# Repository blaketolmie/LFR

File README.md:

# LFR
ENMT221 Line Following Robot Software  
S2 2024  

## Access to Github
Send me your GitHub username or email so I can grant you collaborater access (so you can make push and pull requests etc)  
[GitHub Desktop](https://github.com/apps/desktop)

## Set up  
Download [MiniCore](https://github.com/MCUdude/MiniCore#how-to-install) and make sure its in the correct folder   
Open [Arduino IDE](https://www.arduino.cc/en/software)  
Select Board - ATmega328 and port  
Go to tools and select preferences and burn bootloader  
+ Board: "ATmega328"  
+ BOD (Brown-out detection): "BOD 2.7V"  
+ Bootloader: "Yes (UART0)"  
+ Clock: "Internal 1 MHz"  
+ Variant: "328P / 328PA"  
+ Programmer: "Atmel-ICE ISP"  
>**Arduino as ISP**: If you have an Arduino board, you can use it to program AVR chips by setting it up as an ISP (In-System Programmer). This is a common and cost-effective method.  
>USBasp: This is a popular and inexpensive USB-based programmer for AVR microcontrollers. It's widely used and works well with AVR GCC.  
>USBtinyISP: Another inexpensive USB programmer. It’s often used with AVR microcontrollers but might be slower than USBasp.  
>AVRISP mkII: This is an official programmer from Atmel (now Microchip) designed for use with AVR microcontrollers. It is a reliable choice if you have access to it.  
>Clock: 9.216 MHz  
>[Arduino Programming](https://docs.arduino.cc/programming/)  
>When coding in Arduino IDE use [Arduino Pins](https://camo.githubusercontent.com/b719fa994f4db0dd95e224fbdd939f93f7b6ba881b3c41e480b4733d4d82b6e6/68747470733a2f2f692e696d6775722e636f6d2f715849456368542e6a7067) in blue  
  
## Arduino_Code
Incorporated  
- Reactive control  
- LEDs  
- Sensors  
- Motors  
- Config file - all #defines for pin and globals  
- Serial communication (println)  
  
NOTE:  
Only one reset button (MOTOR_CONTROL) is available since the RESET button is not connect to the microcontroller in the schematic.  
If sensors are giving random values - check the height from the ground  
Only 3 sensors ended up working hence no PID or bang bang controller  
  
 ## ATMega328P Microcontroller
[ATMega328P Features Datasheet](https://components101.com/microcontrollers/atmega328p-pinout-features-datasheet)  
[ATMega328P Manufacteres Datasheet - register summary on pg8](https://www.jameco.com/Jameco/Products/ProdDS/2139111.pdf)

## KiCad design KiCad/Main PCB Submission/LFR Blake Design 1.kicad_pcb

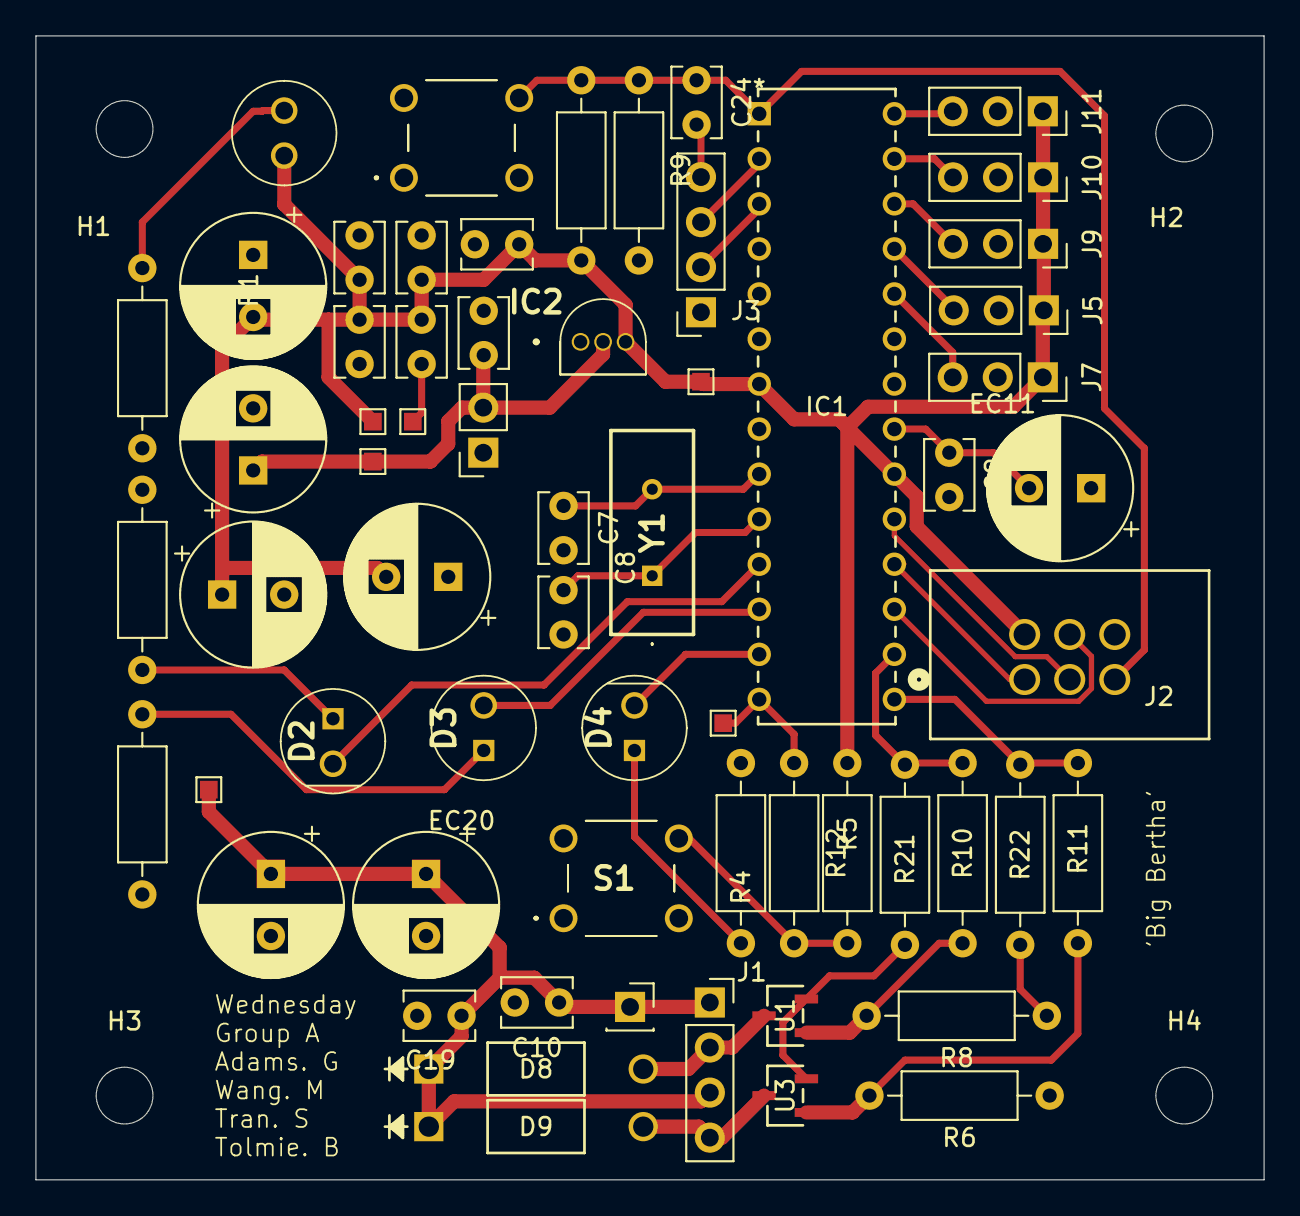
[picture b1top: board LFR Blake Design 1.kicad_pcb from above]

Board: 2 copper layers, 69.2 x 64.5 mm, 66 parts (0 on the bottom side), 34 nets.

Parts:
C2, C3, C5, C9, C14: 100nF; C_Disc_D3.8mm_W2.6mm_P2.50mm
C7, C8: 20pF; C_Disc_D3.8mm_W2.6mm_P2.50mm
C10, C19: 100n; C_Disc_D3.8mm_W2.6mm_P2.50mm
C24: 0.1u; C_Disc_D3.8mm_W2.6mm_P2.50mm
Cm1, Cm2: 100nF; C_Disc_D3.8mm_W2.6mm_P2.50mm
D1: LED; 151051VS04000
D2, D3, D4: LED; 151051BS04000
D8, D9: 1N4004; Diode
EC1, EC4: 10uF; CP_Radial_D8.0mm_P3.50mm
EC11, EC16, EC17: 1uF; CP_Radial_D8.0mm_P3.50mm
EC20, EC21: 100u; CP_Radial_D8.0mm_P3.50mm
H1, H2, H3, H4: MountingHole; MountingHole_3.2mm_M3
IC1: ATMEGA328-PU; Microcontroller
IC2: MCP1700-3302E_TO; MCP17003302ETO
J1: Motor Inputs; PinSocket_1x04_P2.54mm_Vertical
J2: AVR-ISP-6; CONN_WR-BHD_61200621621_WRE
J3: Conn_01x04; PinSocket_1x04_P2.54mm_Vertical
J5, J7, J9, J10, J11: Conn_01x03; PinSocket_1x03_P2.54mm_Vertical
J6: Conn_01x02_Pin; PinSocket_1x02_P2.54mm_Vertical
J8: UnREG; PinSocket_1x01_P2.54mm_Vertical
R1: 360R; Throughhole Resistor
R2, R3, R4: 130; Throughhole Resistor
R5, R7, R21, R22: 10k; Throughhole Resistor
R6, R8, R10, R11: R; Throughhole Resistor
R9, R12: 1k; Throughhole Resistor
S1, S2: MJTP1230
TP1, TP1#2, TP3, TP4, TP5, TP6: TestPoint; TestPoint_Pad_1.0x1.0mm
U1, U3: BSR802NL6327HTSA1; Surface Mount MOSFET
Y1: HC-49_U-S9216000ABJB; HC49US9216000ABJB

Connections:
AVCC: C3.1, C5.1, C14.1, Cm1.1, Cm2.1, D1.2 (A), EC4.1, EC16.2, EC17.2, IC1.7 (VCC), IC1.20 (AVCC), IC2.3 (VOUT), J2.2 (VCC), J5.1, J7.1, J9.1, J10.1, J11.1, R5.2, R7.2, TP1.5 (1), TP3.1
GND: C2.2, C3.2, C5.2, C7.2, C8.2, C9.2, C10.2, C14.2, C19.2, Cm1.2, Cm2.2, EC1.2, EC4.2, EC11.1, EC16.1, EC17.1, EC20.2, EC21.2, IC1.8 (GND_1), IC1.22 (GND_2), IC2.1 (GND), J2.6 (GND), J3.1, J5.2, J6.1, J7.2, J9.2, J10.2, J11.2, R1.2, R2.2, R3.2, R4.2, R6.1, R8.1, R21.1, R22.1, S1.1 (COM_1), S1.4 (NO_2), S2.1 (COM_1), S2.4 (NO_2), TP1#2.1, U1.2, U3.2
MISO: IC1.18 (PB4_(MISO/PCINT4)), J2.1 (MISO)
MOSI: IC1.17 (PB3_(MOSI/OC2A/PCINT3)), J2.4 (MOSI)
MOTOR_CONTROL: IC1.14 ((PCINT0/CLKO/ICP1)_PB0), R12.1, TP4.1
Motor 1: IC1.15 (PB1_(OC1A/PCINT1)), R11.1, R22.2
Motor 2: IC1.16 (PB2_(SS/OC1B/PCINT2)), R10.2, R21.2
unnamed: D1.1 (K), R1.1
unnamed: D2.1 (K), R2.1
unnamed: D3.1 (K), R3.1
unnamed: D4.1 (K), R4.1
unnamed: D8.2 (A), J1.2, U1.3
unnamed: C10.1, C19.1, D8.1 (K), D9.1 (K), EC20.1, EC21.1, J1.1, J1.3, J8.1, TP5.1
unnamed: D9.2 (A), J1.4, U3.3
unnamed: IC1.2 ((PCINT16/RXD)_PD0), J3.3
unnamed: IC1.3 ((PCINT17/TXD)_PD1), J3.2
unnamed: C9.1, EC11.2, IC1.21 (AREF)
unnamed: C24.2, J3.4
unnamed: R8.2, R10.1, U1.1
unnamed: R6.2, R11.2, U3.1
unnamed: R5.1, R12.2, S1.3 (NO_1)
RESET: C24.1, IC1.1 ((PCINT14/RESET)_PC6), J2.5 (~RST), R7.1, R9.1, S2.3 (NO_1)
SCK: IC1.19 (PB5_(SCK/PCINT5)), J2.3 (SCK)
STAT1: D2.2 (A), IC1.11 ((PCINT21/OC0B/T1)_PD5)
STAT2: D3.2 (A), IC1.12 ((PCINT22/OC0A/AIN0)_PD6)
STAT3: D4.2 (A), IC1.13 ((PCINT23/AIN1)_PD7)
Sensor1: IC1.28 (PC5_(ADC5/SCL/PCINT13)), J11.3
Sensor2: IC1.27 (PC4_(ADC4/SDA/PCINT12)), J10.3
Sensor3: IC1.26 (PC3_(ADC3/PCINT11)), J9.3
Sensor4: IC1.25 (PC2_(ADC2/PCINT10)), J5.3
Sensor5: IC1.24 (PC1_(ADC1/PCINT9)), J7.3
UnREG: C2.1, EC1.1, IC2.2 (VIN), J6.2, TP6.1
XIN: C7.1, IC1.9 ((PCINT6/XTAL1/TOSC1)_PB6), Y1.2
XOUT: C8.1, IC1.10 ((PCINT7/XTAL2/TOSC2)_PB7), Y1.1

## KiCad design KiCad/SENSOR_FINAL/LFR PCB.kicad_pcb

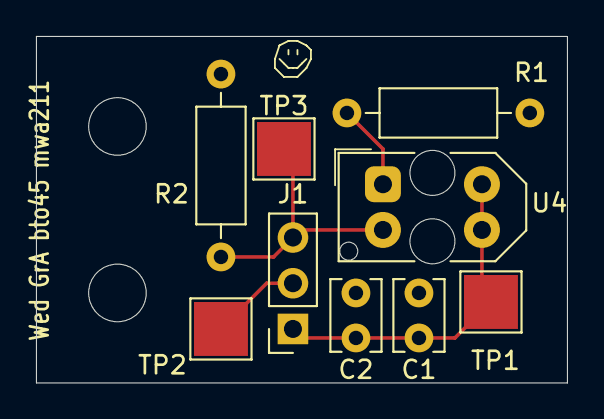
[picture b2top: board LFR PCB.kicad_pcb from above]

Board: 2 copper layers, 29.5 x 19.2 mm, 11 parts (0 on the bottom side), 4 nets.

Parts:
C1: 1uF; C_Disc_D3.8mm_W2.6mm_P2.50mm
C2: 100nF; C_Disc_D3.8mm_W2.6mm_P2.50mm
H1, H2: MountingHole; MountingHole_3.2mm_M3
J1: Conn_01x03_Pin; PinSocket_1x03_P2.54mm_Vertical
R1: 100; Throughhole Resistor
R2: 1.5k; Throughhole Resistor
TP1, TP2, TP3: TestPoint; TestPoint_Pad_3.0x3.0mm
U4: TCRT5000; Sensor

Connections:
GND: C1.2, C2.2, J1.2, R1.2, R2.2, TP2.1
unnamed: R1.1, U4.1 (C)
Sensor: J1.3, R2.1, TP3.1, U4.2 (E)
VCC: C1.1, C2.1, J1.1, TP1.1, U4.3 (A), U4.4 (C)

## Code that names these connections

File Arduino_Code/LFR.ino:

#include <Arduino.h>
// https://docs.arduino.cc/programming/
#define SENSOR_COUNT 5

// PID constants
#define Kp 2.0                 // Proportional
#define Ki 1.0                 // Integral
#define Kd 1.0                 // Derivative

// ADC channels for sensors (use analogRead on Arduino)
#define SENSOR_1 A0            // Pin 23
#define SENSOR_2 A1            // Pin 24
#define SENSOR_3 A2            // Pin 25 (Middle sensor)
#define SENSOR_4 A3            // Pin 26
#define SENSOR_5 A4            // Pin 27

#define SETPOINT 255           // Setpoint for the middle sensor (ideally 255)

// Motor speed limits
#define MAX_MOTOR_SPEED 255
#define MIN_MOTOR_SPEED 0
#define INTEGRAL_LIMIT 100     // Limit for the integral term to prevent windup

void initMotors();                             // Initialize motor outputs
void setMotorSpeed(int16_t leftSpeed, int16_t rightSpeed); // Set motor speeds
int16_t calculatePID(int16_t error);          // Calculate PID correction
void initStatLEDs();                           // Initializes Status LEDs
void turnOnLED(int ledNumber);                 // Turns on specified LED
void turnOffLED(int ledNumber);                // Turns off specified LED

void setup() {
    initStatLEDs();                             // Initialize LEDs
    initMotors();                               // Initialize motors
}

void loop() {
    int16_t sensorValues[SENSOR_COUNT];        // Array to hold sensor values

    // Read sensor values
    for (int i = 0; i < SENSOR_COUNT; i++) {
        sensorValues[i] = analogRead(A0 + i);  // Read sensors from A0 to A4
    }

    int16_t error = SETPOINT - sensorValues[2]; // Calculate error
    int16_t pid = calculatePID(error);           // Calculate PID value

    int16_t leftMotorSpeed = 127 + pid;         // Adjust left motor speed
    int16_t rightMotorSpeed = 127 - pid;        // Adjust right motor speed

    // Clamp motor speed values to defined limits
    leftMotorSpeed = constrain(leftMotorSpeed, MIN_MOTOR_SPEED, MAX_MOTOR_SPEED);
    rightMotorSpeed = constrain(rightMotorSpeed, MIN_MOTOR_SPEED, MAX_MOTOR_SPEED);

    setMotorSpeed(leftMotorSpeed, rightMotorSpeed); // Set motor speeds
    delay(100);                                    // Delay for stability
}

void initMotors() {
    pinMode(15, OUTPUT); // Set pin 15 as output for left motor control (Motor 1)
    pinMode(16, OUTPUT); // Set pin 16 as output for right motor control (Motor 2)
}

void setMotorSpeed(int16_t leftSpeed, int16_t rightSpeed) {
    analogWrite(15, leftSpeed);   // Set left motor speed (connected to pin 15)
    analogWrite(16, rightSpeed);   // Set right motor speed (connected to pin 16)
}

int16_t calculatePID(int16_t error) {
    static int16_t prev_error = 0; // Previous error for derivative
    static int16_t integral = 0;    // Integral accumulator

    // Calculate integral with clamping
    integral += error;
    integral = constrain(integral, -INTEGRAL_LIMIT, INTEGRAL_LIMIT);

    // Calculate derivative
    int16_t derivative = error - prev_error;

    // Calculate PID output
    int16_t pid_output = (Kp * error) + (Ki * integral) + (Kd * derivative);

    // Store current error as previous error
    prev_error = error;

    return pid_output; // Return PID correction value
}

void initStatLEDs() {
    pinMode(11, OUTPUT); // Set pin 11 as output for LED1 (STAT1)
    pinMode(12, OUTPUT); // Set pin 12 as output for LED2 (STAT2)
    pinMode(13, OUTPUT); // Set pin 13 as output for LED3 (STAT3)
}

void turnOnLED(int ledNumber) {
    digitalWrite(ledNumber, HIGH); // Turns on specified LED
}

void turnOffLED(int ledNumber) {
    digitalWrite(ledNumber, LOW); // Turns off specified LED
}

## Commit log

2024-10-02 uploaded v1 of LFR.c, readme was updated
    Updated LFR.c
    Updated REAME.md
    LFR.c still quite buggy / needs more work and refining
2024-10-03 include AVR files for reference
2024-10-03 added avr for reference
2024-10-03 Create avr-libc
2024-10-06 Adding KiCad files
2024-10-06 Changed to Arduino Programming
    Instead of doing C changed it to Arduino programming using ChatGPT so need to fix bugs and pin numbers etc
2024-10-06 update with correct pin numbers
2024-10-06 Modularized the code
    Modularized the code into different sections
2024-10-06 Organized folders
2024-10-06 blinking light added
2024-10-08 Made it so then it works using Arduino IDE
    Needed to rename and move files so then all the .cpp and .h files open in Arduino IDE
2024-10-10 Update LFR_LED
2024-10-14 BANG BANG CONTROLLER ADDED
2024-10-14 moved pid code into old code folder
2024-10-14 updated set motor speed to include constraining speed
2024-10-14 update config
2024-10-15 WORKING VERSION - 2 Sensors
2024-10-15 16/10/2024 Working code
2024-10-16 Made code look nice for screenshots
2024-10-16 Updated name
2024-10-21 removed old PID
2024-10-21 folder reshuffle
2024-10-21 Fixed
2024-10-21 working version
2024-10-21 Update template
2024-10-21 Working
